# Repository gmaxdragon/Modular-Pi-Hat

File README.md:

# Modular PI HAT

> **24 October 2026 technical audit:** Both the [main KiCad project](hardware/main/test1.kicad_pro) and [servo-extender KiCad project](hardware/servo-extender/SZSERVOEXTENDER.kicad_pro), plus their separate Gerber/drill packages, are present in this repository. These are **unassembled design files**. The archived $79.05 figure includes **$30 estimated shipping**, excludes tax and unlisted material, and is not a live manufacturing quote. The selected 2A servo fuse, 3.3V regulator thermal/load margin, USB connector land pattern, stacking/header clearances and 4-wire extender cable still require physical review before energizing the robot. The OLED pin sequence differs from J10 and must be individually remapped, never plugged directly. [Detailed engineering release gates](docs/ENGINEERING_RELEASE_GATES_2026-10-24.md). This note is technical and leaves the owner's original project narrative intact.

## What I made

I made a massive PCB which is a PI Hat for my robotic arm. I really wanted to streamline everything and shrink it down and make it more reliable so I made this. It's really cool.

## What it does

The big board is a massive PI Hat that can control servos, attach to sensors, and connect to the mini board which is connected by a big cable to the main board on screw terminals and it controls 2 servos for the wrist and gripper.

## Why I made it

I made it because I was having a ton of difficulties making everything move correctly and everything was all over the place. It's way simpler, easy to use, and reliable.

## My work and what I learned

I personally worked on the schematics and routing and basically, I added all the components, added power symbols, added net labels, and multiple more stuff and routed and adjusted the whole PCB. I worked through a lot of problems such as the ERCs not budging, a ton of short circuits reported in the DRC and a ton of more annoying problems. However, I learned the whole flow of how to make a schematic and a PCB and it feels really good now.

## Current status

Currently, the whole board is finished. The schematics, the routing, and testing is all good now. Nothing has been made as of now and I need to test it out and solder it once it comes.

## Help and sources

I used AI a ton in order to guide me with making the full thing and giving me instructions on how to fix some errors. Mostly, I used the ERC and DRC a ton as it's extremely helpful for me and it pinpoints where all the errors are and I used the help of some friends in school to tell me what to do. Honestly, AI helped with making the schematics and telling me what parts I need and researching meanwhile I did the work, it helped me with organizing and kicking off routing the board, it helped me when there was annoying footprint issues, and a ton of error fixing and instructions.

## Journal note

Hey, I accidentally added Week 3 one of the journal entries here, don't mind it please. I couldn't find a way to remove it.

## Bill of materials

PCB fabrication is $4.00 per board. This table includes one main PCB and one servo-extender PCB. Shipping remains the existing $30.00 estimate.

| Item | Qty | Supplier | Cost/item (USD) | Total cost (USD) | Link |
| --- | ---: | --- | ---: | ---: | --- |
| ESP32-S3-WROOM-1-N8R8 module, 8MB flash + 8MB PSRAM | 1 | Mouser | $6.28 | $6.28 | [Part](https://www.mouser.com/en/ProductDetail/Espressif-Systems/ESP32-S3-WROOM-1-N8R8?qs=7D1LtPJG0i3%2F28hKFavOpQ%3D%3D) |
| AP2112K-3.3 3.3 V LDO regulator | 1 | DigiKey | $0.28 | $0.28 | [Part](https://www.digikey.com/en/products/detail/diodes-incorporated/AP2112K-3-3TRG1/4470746) |
| 40-pin extra-tall 2x20 female stacking header | 1 | DigiKey | $2.95 | $2.95 | [Part](https://www.digikey.com/en/products/detail/adafruit-industries-llc/1979/6238003) |
| 4-way 5.08 mm Phoenix screw terminal | 2 | DigiKey | $2.28 | $4.56 | [Part](https://www.digikey.com/en/products/detail/phoenix-contact/1715747/260633) |
| 2-way 5.08 mm Phoenix screw terminal | 1 | DigiKey | $1.16 | $1.16 | [Part](https://www.digikey.com/en/products/detail/phoenix-contact/1715721/260631) |
| Breakaway 0.1 inch male pin header strips, 10-pack | 1 | DigiKey | $4.95 | $4.95 | [Part](https://www.digikey.com/en/products/detail/adafruit-industries-llc/392/21283800) |
| USB-C USB2.0 receptacle | 1 | DigiKey | $0.80 | $0.80 | [Part](https://www.digikey.com/en/products/detail/gct/USB4105-GF-A/11198441) |
| 470 uF 10 V through-hole capacitor | 1 | DigiKey | $0.71 | $0.71 | [Part](https://www.digikey.com/en/products/detail/panasonic-industry/EEU-FR1A471/9921021) |
| 100 uF 25 V through-hole capacitor | 1 | DigiKey | $0.87 | $0.87 | [Part](https://www.digikey.com/en/products/detail/kyocera-avx/RPA0609101M025B/17634433) |
| 22 uF 10 V 1206 ceramic capacitor | 1 | DigiKey | $0.47 | $0.47 | [Part](https://www.digikey.com/en/products/detail/samsung-electro-mechanics/CL31A226KPHNNNE/3886945) |
| 1 uF 50 V 0805 ceramic capacitor | 3 | DigiKey | $0.18 | $0.54 | [Part](https://www.digikey.com/en/products/detail/samsung-electro-mechanics/CL21A105KBCLNNC/3888054) |
| 100 nF 50 V 0805 ceramic capacitor | 1 | DigiKey | $0.10 | $0.10 | [Part](https://www.digikey.com/en/products/detail/samsung-electro-mechanics/CL21B104KBCNNNC/3886661) |
| 10k 1 percent 0805 resistor | 4 | DigiKey | $0.10 | $0.40 | [Part](https://www.digikey.com/en/products/detail/yageo/RC0805FR-0710KL/727535) |
| 5.1k 1 percent 0805 resistor | 2 | DigiKey | $0.10 | $0.20 | [Part](https://www.digikey.com/en/products/detail/bourns-inc/CR0805-FX-5101ELF/4247942) |
| 22 ohm 1 percent 0805 resistor | 2 | DigiKey | $0.10 | $0.20 | [Part](https://www.digikey.com/en/products/detail/yageo/RC0805FR-0722RL/727735) |
| 1k 1 percent 0805 resistor | 1 | DigiKey | $0.10 | $0.10 | [Part](https://www.digikey.com/en/products/detail/yageo/RC0805FR-071KL/727444) |
| 75k 1 percent 0805 resistor | 1 | DigiKey | $0.10 | $0.10 | [Part](https://www.digikey.com/en/products/detail/yageo/RC0805FR-0775KL/731080) |
| 100k 1 percent 0805 resistor | 1 | DigiKey | $0.11 | $0.11 | [Part](https://www.digikey.com/en/products/detail/yageo/RC0805FR-07100KL/727544) |
| 4.7k 1 percent 0805 resistor | 2 | DigiKey | $0.10 | $0.20 | [Part](https://www.digikey.com/en/products/detail/yageo/RC0805FR-074K7L/727929) |
| Green 0805 LED | 1 | DigiKey | $0.19 | $0.19 | [Part](https://www.digikey.com/en/products/detail/lite-on-inc/LTST-C170KGKT/386777) |
| SPST SMD tactile switch | 2 | DigiKey | $0.21 | $0.42 | [Part](https://www.digikey.com/en/products/detail/e-switch/TL3305AF160QG/5816181) |
| Keystone mini blade through-hole fuse holder | 1 | DigiKey | $1.31 | $1.31 | [Part](https://www.digikey.com/en/products/detail/keystone-electronics/3568/2137306) |
| Littelfuse MINI 297 2A 32V blade fuse, selected for prototype | 1 | DigiKey | $0.39 | $0.39 | [Part](https://www.digikey.com/en/products/detail/littelfuse-inc/0297002-WXNV/124900) |
| 0.91 inch white 128x32 SSD1306 I2C OLED breakout, DFRobot DFR0648 | 1 | DigiKey | $9.90 | $9.90 | [Part](https://www.digikey.com/en/products/detail/dfrobot/DFR0648/12324932) |
| 4-position 2.54mm Samtec OLED female socket | 1 | DigiKey | $1.11 | $1.11 | [Part](https://www.digikey.com/en/products/detail/samtec-inc/SSW-104-01-G-S/1112103) |
| 6 inch male-to-female jumper cable kit, 20 wires, for OLED J10 pin-order correction | 1 | DigiKey | $2.75 | $2.75 | [Part](https://www.digikey.com/en/products/detail/sparkfun-electronics/12794/5993859) |
| Main PCB fabrication, 1 bare board | 1 | JLCPCB | $4.00 | $4.00 | [Ordering reference](https://jlcpcb.com/help/article/how-do-i-place-an-order) |
| Servo extender PCB fabrication, 1 bare board | 1 | JLCPCB | $4.00 | $4.00 | [Ordering reference](https://jlcpcb.com/help/article/how-do-i-place-an-order) |
| **Parts and boards subtotal** | | | | **$49.05** | |
| Estimated total shipping | 1 | | | $30.00 | |
| **Total including estimated shipping** | | | | **$79.05** | |

[BOM.csv](BOM.csv) contains the same items and prices. [bom.csv](bom.csv) includes part numbers and assembly notes. Tax, customs and unlisted wiring costs are not included in the total above.

## Design files

| Board | Schematic | PCB | KiCad project | Gerbers and drills |
| --- | --- | --- | --- | --- |
| Main Pi HAT | [Schematic](hardware/main/test1.kicad_sch) | [PCB](hardware/main/test1.kicad_pcb) | [Project](hardware/main/test1.kicad_pro) | [ZIP](fabrication/main/Seizo_Main_HAT_Gerbers.zip) |
| Servo extender | [Schematic](hardware/servo-extender/SZSERVOEXTENDER.kicad_sch) | [PCB](hardware/servo-extender/SZSERVOEXTENDER.kicad_pcb) | [Project](hardware/servo-extender/SZSERVOEXTENDER.kicad_pro) | [ZIP](fabrication/servo-extender/Seizo_Servo_Extender_Gerbers.zip) |

[Footprint library](hardware/main/Seizo_Reviewed.pretty) · [Footprint library table](hardware/main/fp-lib-table) · [Journal](JOURNAL.md) · [Parts and wiring notes](purchasing/README.md) · [Fabrication notes](fabrication/GERBER_EXPORT_README.md)

[USB diagnostic firmware](firmware/seizo_diagnostics/seizo_diagnostics.ino): AI-assisted; not compiled for the ESP32 target or tested on hardware yet.

## Project images

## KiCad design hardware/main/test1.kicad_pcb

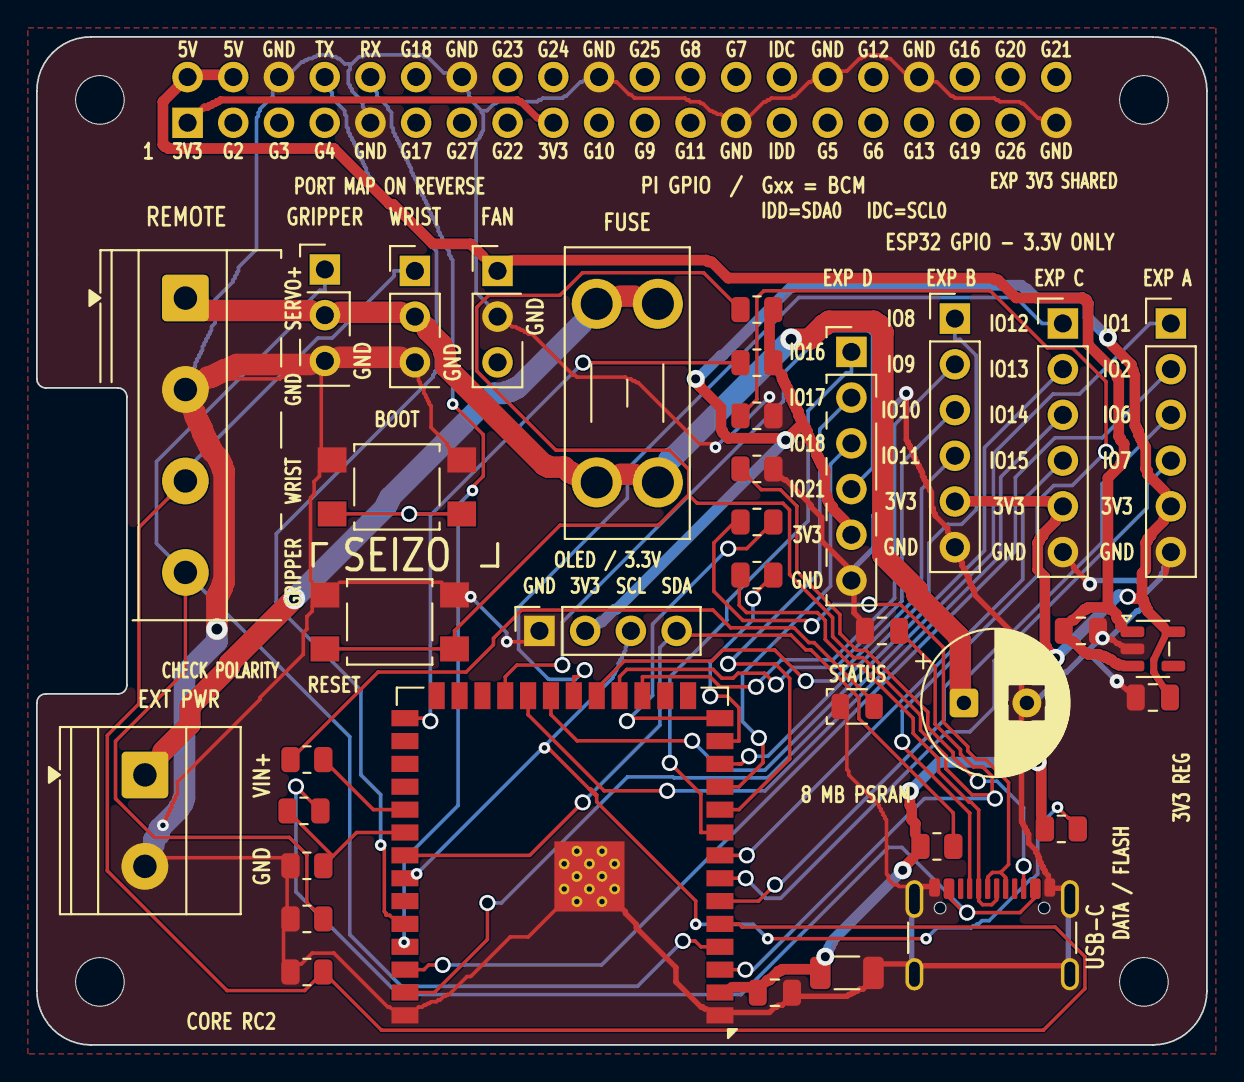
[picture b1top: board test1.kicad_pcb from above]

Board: 2 copper layers, 65.0 x 56.0 mm, 41 parts (1 on the bottom side), 40 nets.

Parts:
C2: 1uF; RC2_C2_C_0805_2012Metric
C3: 470uF; RC2_C3_CP_Radial_D8_0mm_P3_50mm
C4: 22uF; RC2_C4_C_1206_3216Metric
C5: 100nF; RC2_C5_C_0805_2012Metric
C7: 1uF; RC2_C7_C_0805_2012Metric
C8: 1uF; RC2_C8_C_0805_2012Metric
D1: LED; RC2_D1_LED_0805_2012Metric
F1: Fuse; RC2_F1_Fuseholder_Blade_Mini_Keystone_3568
J1: GPIO; Pi_HAT_Stacking_Socket_Checked
J2: Gripper; RC2_J2_PinHeader_1x03_P2_54mm_Vertical
J3: Wrist; RC2_J3_PinHeader_1x03_P2_54mm_Vertical
J4: Conn_01x06; RC2_J4_PinHeader_1x06_P2_54mm_Vertical
J5: Conn_01x06; RC2_J5_PinHeader_1x06_P2_54mm_Vertical
J6: Conn_01x06; RC2_J6_PinHeader_1x06_P2_54mm_Vertical
J7: Conn_01x06; RC2_J7_PinHeader_1x06_P2_54mm_Vertical
J8: USB_C_Receptacle_USB2.0_16P; RC2_J8_USB4105_GND_Heel_Clearance
J9: Screw_Terminal_01x02; RC2_J9_TerminalBlock_Phoenix_MKDS_1_5_2_5_08_1x02_P5_08mm_H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
J10: ONBOARD_OLED; RC2_J10_PinSocket_1x04_P2_54mm_Vertical
J11: REMOTE_SERVO_CABLE; RC2_J11_Servo_Terminal_Silk_Clipped
J12: PI_FAN; RC2_J12_PinHeader_1x03_P2_54mm_Vertical
MH1, MH2, MH3, MH4: MountingHole_2.7mm_M2.5
R3: 10K; RC2_R3_R_0805_2012Metric
R4: 10k; RC2_R4_R_0805_2012Metric
R5: 5.1k; RC2_R5_R_0805_2012Metric
R6: 5.1k; RC2_R6_R_0805_2012Metric
R7: 22; RC2_R7_R_0805_2012Metric
R8: 22; RC2_R8_R_0805_2012Metric
R9: 1k; RC2_R9_R_0805_2012Metric
R10: 75k; RC2_R10_R_0805_2012Metric
R11: 100k; RC2_R11_R_0805_2012Metric
R12: 10k; RC2_R12_R_0805_2012Metric
R13: 10k; RC2_R13_R_0805_2012Metric
R14: 4.7k; RC2_R14_R_0805_2012Metric
R15: 4.7k; RC2_R15_R_0805_2012Metric
RESET1: SW_Push; RC2_RESET1_SW_SPST_TL3305A
SW1: SW_Push; RC2_SW1_SW_SPST_TL3305A
U2: ESP32-S3-WROOM-1-N8R8; RC2_U2_ESP32_S3_WROOM_1_Thermal030
U3: AP2112K-3.3; RC2_U3_SOT_23_5

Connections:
+3V3: J1.1, J1.17
+5V: C7.1, J1.2, J1.4, J12.1, U3.1 (VIN), U3.3 (EN)
/BOARD_3V3: C4.1, C5.1, C8.1, J4.5, J5.5, J6.5, J7.5, J10.2, R3.2, R4.2, R14.1, R15.1, U2.2 (3V3), U3.5 (VOUT)
/GPIO_A1: J4.1, U2.39 (IO1)
/GPIO_A2: J4.2, U2.38 (IO2)
/GPIO_A3: J4.3, U2.6 (IO6)
/GPIO_A4: J4.4, U2.7 (IO7)
/GPIO_B1: J6.1, U2.12 (IO8)
/GPIO_B2: J6.2, U2.17 (IO9)
/GPIO_B3: J6.3, U2.18 (IO10)
/GPIO_B4: J6.4, U2.19 (IO11)
/GPIO_C1: J5.1, U2.20 (IO12)
/GPIO_C2: J5.2, U2.21 (IO13)
/GPIO_C3: J5.3, U2.22 (IO14)
/GPIO_C4: J5.4, U2.8 (IO15)
/GPIO_D1: J7.1, U2.9 (IO16)
/GPIO_D2: J7.2, U2.10 (IO17)
/GPIO_D3: J7.3, U2.11 (IO18)
/GPIO_D4: J7.4, U2.23 (IO21)
/GRIPPER_SIG: J2.1, J11.4, R12.2, U2.4 (IO4)
/IO19: R8.2, U2.13 (USB_D-)
/IO20: R7.2, U2.14 (USB_D+)
/OLED_SCL: J10.3, R15.2, U2.34 (IO41)
/OLED_SDA: J10.4, R14.2, U2.33 (IO40)
/PI_UART_RX: J1.10, U2.37 (TXD0)
/PI_UART_TX: J1.8, U2.36 (RXD0)
/SERVO_IN+: F1.2, J9.1
/SERVO_V+: C3.1, F1.1, J2.2, J3.2, J11.1
/STATUS_LED: R9.2, U2.31 (IO38)
/USB-VBUS_SENSE: R10.1, R11.2, U2.32 (IO39)
/WRIST_SIG: J3.1, J11.3, R13.2, U2.5 (IO5)
GND: C2.1, C3.2, C4.2, C5.2, C7.2, C8.2, D1.1 (K), J1.6, J1.9, J1.14, J1.20, J1.25, J1.30, J1.34, J1.39, J2.3, J3.3, J4.6, J5.6, J6.6, J7.6, J8.A1 (GND), J8.A12 (GND), J8.B1 (GND), J8.B12 (GND), J8.SH (SHIELD), J9.2, J10.1, J11.2, J12.2, R5.2, R6.2, R11.1, R12.1, R13.1, RESET1.1, SW1.1, U2.1 (GND), U2.40 (GND), U2.41 (GND), U3.2 (GND)
unnamed: D1.2 (A), R9.1
unnamed: J8.A5 (CC1), R5.1
unnamed: J8.B5 (CC2), R6.1
unnamed: J8.A6 (D+), J8.B6 (D+), R7.1
unnamed: J8.A7 (D-), J8.B7 (D-), R8.1
unnamed: J8.A4 (VBUS), J8.A9 (VBUS), J8.B4 (VBUS), J8.B9 (VBUS), R10.2
unnamed: C2.2, R3.1, RESET1.2, U2.3 (EN)
unnamed: R4.1, SW1.2, U2.27 (IO0)

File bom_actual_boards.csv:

Board,References,Description,Quantity,Manufacturer,Manufacturer_Part_Number,DigiKey_Part_Number,Unit_USD,Extended_USD,Status,Notes
MAIN,J11; EXT J1,4-position 5.08 mm terminal,2,Phoenix Contact,1715747,277-1265-ND,2.28,4.56,CART_CONFIRMED,"2 total, fits both boards"
MAIN,MAIN J9,2-position 5.08 mm terminal,1,Phoenix Contact,1715721,277-1263-ND,1.16,1.16,CART_CONFIRMED,Servo supply inlet
MAIN,MAIN J10,4-pin female OLED socket 0.1 inch,1,Samtec,SSW-104-01-G-S,612-SSW-104-01-G-S-ND,1.11,1.11,CART_CONFIRMED,Check OLED pin orientation and socket body
MAIN,MAIN C3,470uF 10V radial 3.50mm pitch,1,Panasonic,EEU-FR1A471,P124219-ND,0.71,0.71,CART_CONFIRMED,Polarized
EXT,EXT C1,100uF 25V radial polymer 2.50mm pitch,1,KYOCERA AVX,RPA0609101M025B,478-RPA0609101M025B-ND,0.87,0.87,CART_CONFIRMED,Polarized
MAIN,MAIN F1,2A 32V MINI blade fuse,1,Littelfuse,0297002.WXNV,F986-ND,0.39,0.39,CART_CONFIRMED_PROVISIONAL_RATING,Fits MINI blade fuseholder; rated 2A needs servo stall current validation
MAIN,MAIN U3,3.3V SOT-23-5 LDO,1,Diodes Inc,AP2112K-3.3TRG1,AP2112K-3.3TRG1CT-ND,0.28,0.28,SKU_VERIFIED_BY_PAGE_FAMILY,Cut tape replace ATR/TR quantity error; regulator thermal budget unresolved
MAIN,MAIN J1,Raspberry Pi extra-tall 40-pin stacking socket,1,Adafruit,1979,1528-1783-ND,2.95,2.95,SKU_WEB_VERIFIED,Do not use 1979 as DigiKey SKU; check underside geometry
MAIN,MAIN J8,USB-C 16-pin right-angle connector,1,GCT,USB4105-GF-A,2073-USB4105-GF-ACT-ND,0.80,0.80,SKU_WEB_VERIFIED,Custom land pattern mechanical check required
MAIN,MAIN C4,22uF 10V X5R 1206,1,Samsung,CL31A226KPHNNNE,1276-1287-1-ND,0.47,0.47,SKU_PROVISIONAL,Verify cut-tape suffix against DigiKey page before purchase
MAIN,MAIN C2 C7 C8,1uF 50V X5R 0805,3,Samsung,CL21A105KBCLNNC,1276-2396-1-ND,0.18,0.54,SKU_PROVISIONAL,Verify cut-tape suffix against DigiKey page before purchase
MAIN,MAIN C5,100nF 50V X7R 0805,1,Samsung,CL21B104KBCNNNC,1276-1003-1-ND,0.10,0.10,SKU_PROVISIONAL,Verify cut-tape suffix against DigiKey page before purchase
MAIN,MAIN R3 R4 R12 R13,10k 1% 0805 resistors,4,Yageo,RC0805FR-0710KL,311-10.0KCRCT-ND,0.10,0.40,SKU_PROVISIONAL,Replace reel SKU; verify exact CT SKU
MAIN,MAIN R14 R15,4.7k 1% 0805 resistors,2,Yageo,RC0805FR-074K7L,311-4.70KCRCT-ND,0.10,0.20,SKU_PROVISIONAL,Replace reel SKU; verify exact CT SKU
MAIN,MAIN R5 R6,5.1k 1% 0805 resistors,2,Bourns,CR0805-FX-5101ELF,CR0805-FX-5101ELFCT-ND,0.10,0.20,SKU_WEB_VERIFIED,USB-C CC pulldowns
MAIN,MAIN R7 R8,22 ohm 1% 0805 resistors,2,Yageo,RC0805FR-0722RL,311-22.0CRCT-ND,0.10,0.20,SKU_PROVISIONAL,Verify exact cut-tape DigiKey code
MAIN,MAIN R9,1k 1% 0805 resistor,1,Yageo,RC0805FR-071KL,311-1.00KCRCT-ND,0.10,0.10,SKU_PROVISIONAL,Verify exact cut-tape DigiKey code
MAIN,MAIN R10,75k 1% 0805 resistor,1,Yageo,RC0805FR-0775KL,311-75.0KCRCT-ND,0.10,0.10,SKU_PROVISIONAL,Replaces wrong 100k quantity; verify CT
MAIN,MAIN R11,100k 1% 0805 resistor,1,Yageo,RC0805FR-07100KL,311-100KCRCT-ND,0.11,0.11,SKU_PROVISIONAL,Only ONE 100k required
MAIN,MAIN D1,Green 0805 LED,1,Lite-On,LTST-C170KGKT,160-1414-1-ND,0.19,0.19,SKU_PROVISIONAL,"Verify CT suffix, polarity"
MAIN,MAIN SW1 RESET1,SMD tactile switch TL3305A,2,E-Switch,TL3305AF160QG,EG5350CT-ND,0.20,0.40,SKU_PROVISIONAL,Verify exact cut-tape SKU and footprint
MAIN+EXT,MAIN J2 J3 J4 J5 J6 J7 J12; EXT J2 J3,Male 0.1 inch breakaway headers (39 pins total),1,Adafruit,392,1528-1370-ND,4.95,4.95,SKU_PROVISIONAL,One 10 x 36-pin strip PACK; verify actual packaging and MPN
MAIN,MAIN U2,ESP32-S3-WROOM-1-N8R8 8MB PSRAM module,1,Espressif,ESP32-S3-WROOM-1-N8R8,5407-ESP32-S3-WROOM-1-N8R8CT-ND,6.32,6.32,DEFERRED_EXCLUDED_FROM_ORDER,Not in immediate cart at user request. Board cannot function without this module.
MAIN,MAIN J10 accessory,0.96in I2C OLED display 3.3V,1,TBD,TBD,,0.00,0.00,UNSELECTED,Connector is on PCB. Buy module only if not already owned; check GND VCC SCL SDA.

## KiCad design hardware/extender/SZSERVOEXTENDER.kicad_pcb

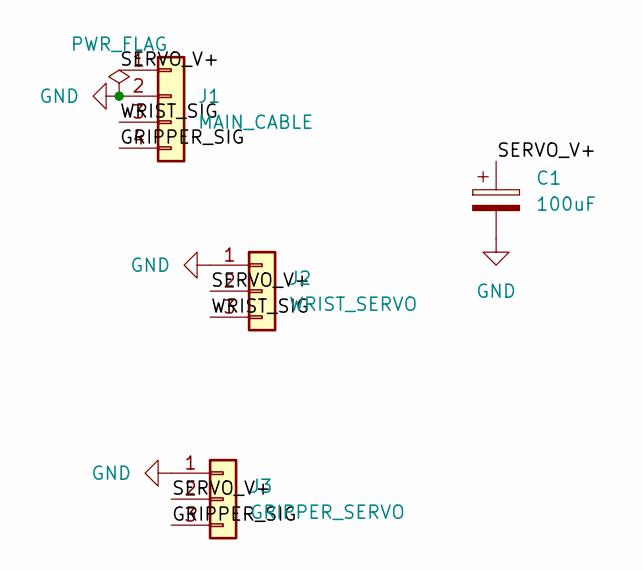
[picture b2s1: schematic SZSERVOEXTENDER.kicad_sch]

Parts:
C1: 100uF; CP_Radial_D6.3mm_P2.50mm
J1: MAIN_CABLE; TerminalBlock_Phoenix_MKDS-1,5-4-5.08_1x04_P5.08mm_Horizont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
J2: WRIST_SERVO; PinHeader_1x03_P2.54mm_Vertical
J3: GRIPPER_SERVO; PinHeader_1x03_P2.54mm_Vertical

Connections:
/GRIPPER_SIG: J1.4, J3.3
/SERVO_V+: C1.1, J1.1, J2.2, J3.2
/WRIST_SIG: J1.3, J2.3
GND: C1.2, J1.2, J2.1, J3.1

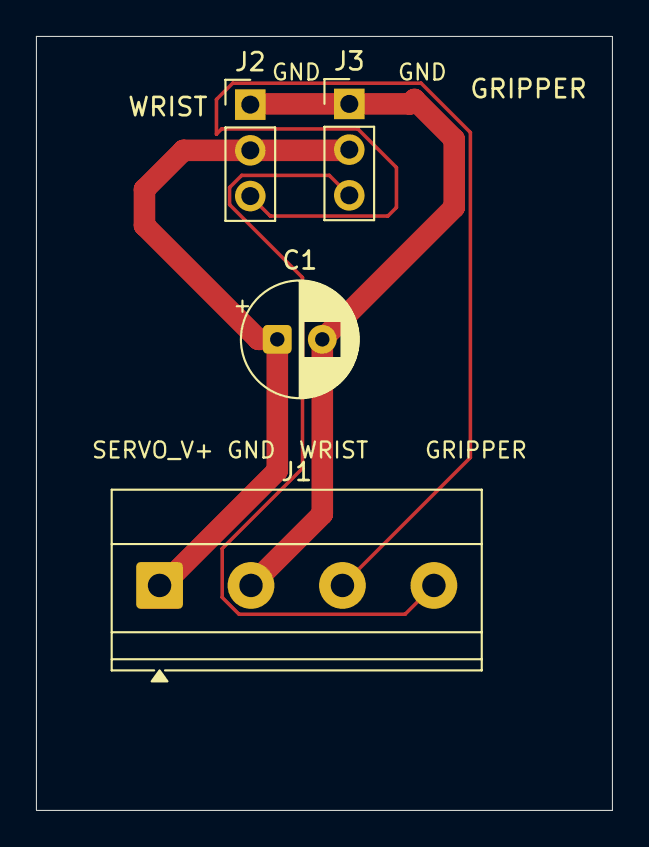
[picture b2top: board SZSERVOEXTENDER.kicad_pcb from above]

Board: 2 copper layers, 32.0 x 43.0 mm, 4 parts (0 on the bottom side), 4 nets.
